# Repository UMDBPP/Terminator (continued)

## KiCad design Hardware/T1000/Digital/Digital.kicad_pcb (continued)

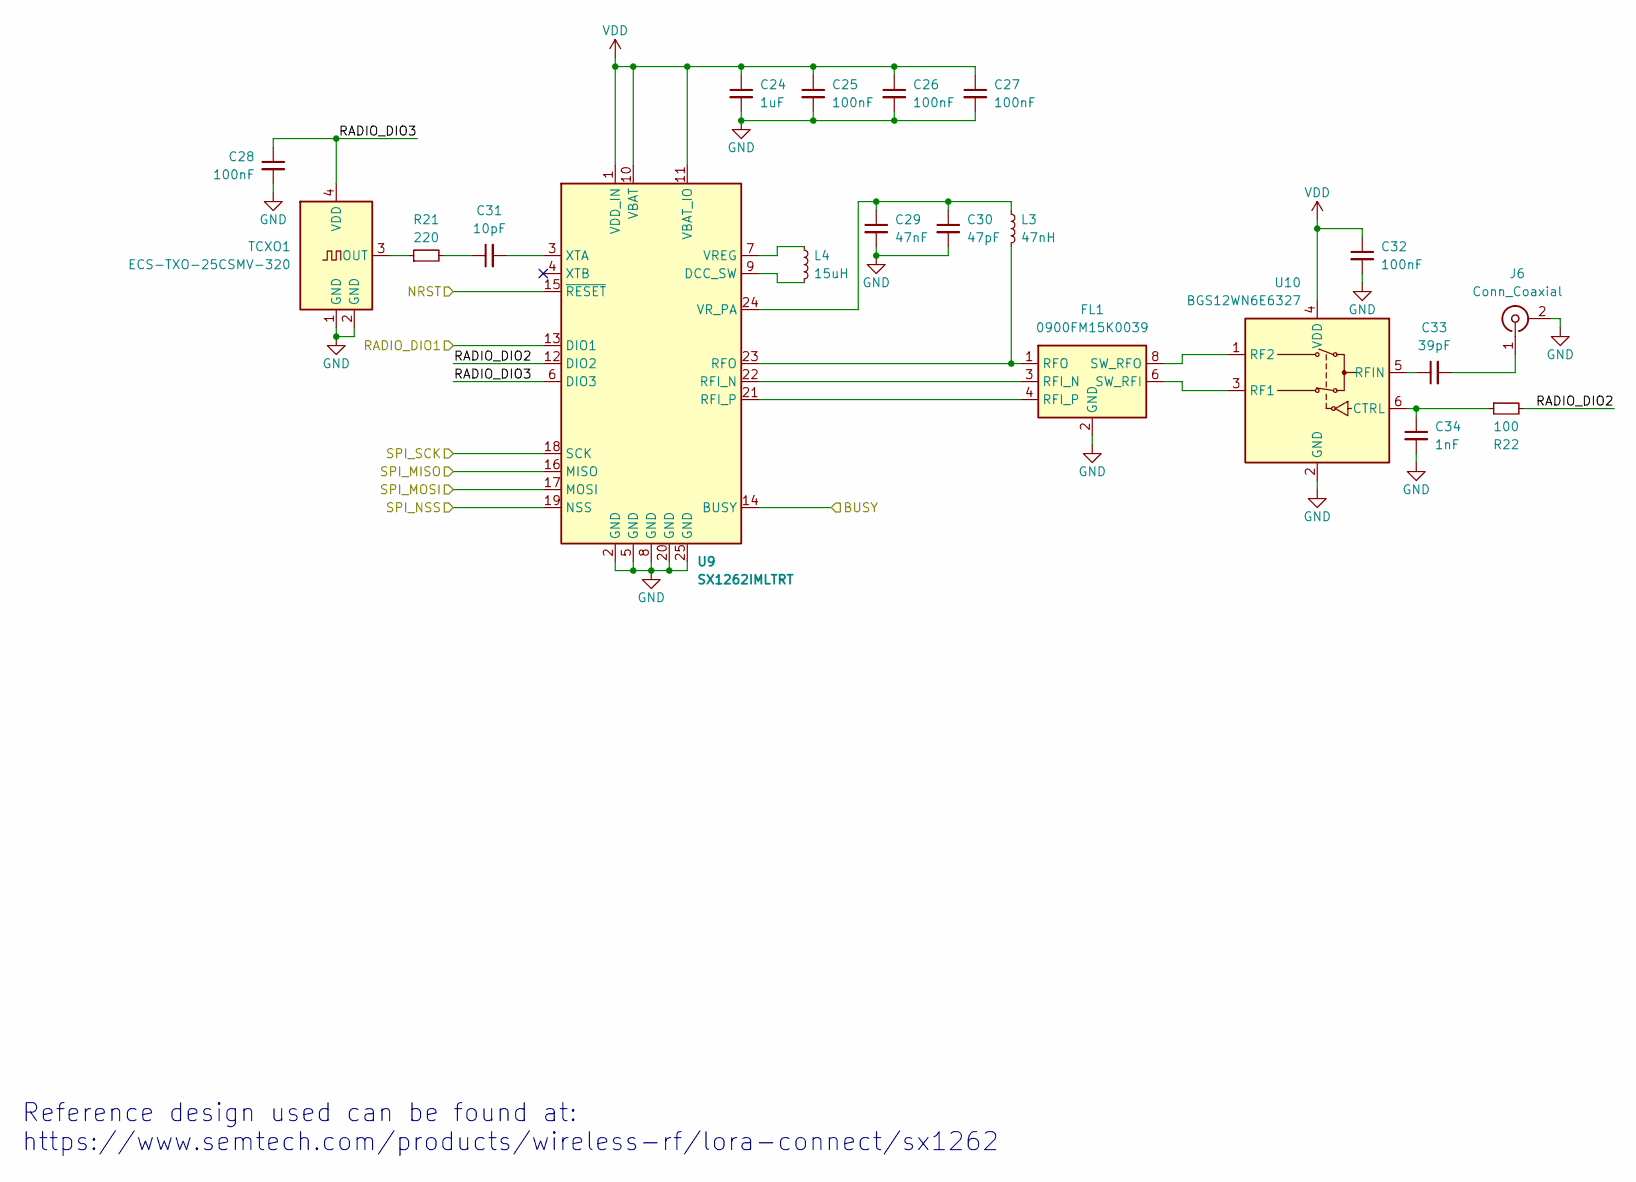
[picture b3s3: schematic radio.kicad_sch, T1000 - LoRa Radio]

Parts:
C24: 1uF; C_0603_1608Metric
C25, C26, C27, C28, C32: 100nF; C_0402_1005Metric
C29: 47nF; C_0402_1005Metric
C30: 47pF; C_0402_1005Metric
C31: 10pF; C_0402_1005Metric
C33: 39pF; C_0402_1005Metric
C34: 1nF; C_0402_1005Metric
FL1: 0900FM15K0039; Balun_Johanson_0900FM15K0039
J6: Conn_Coaxial; U.FL_Molex_MCRF_73412-0110_Vertical
L3: 47nH; L_0402_1005Metric
L4: 15uH; L_0805_2012Metric
R21: 220; R_0402_1005Metric
R22: 100; R_0402_1005Metric
TCXO1: ECS-TXO-25CSMV-320; Crystal_SMD_2520-4Pin_2.5x2.0mm
U9: SX1262IMLTRT; QFN-24-1EP_4x4mm_P0.5mm_EP2.6x2.6mm
U10: BGS12WN6E6327; Infineon_PG-TSNP-6-10_0.7x1.1mm_0.7x1.1mm_P0.4mm

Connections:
/LoRa Radio/RADIO_DIO2: R22.2, U9.12 (DIO2)
/LoRa Radio/RADIO_DIO3: C28.1, TCXO1.4 (VDD), U9.6 (DIO3)
/RADIO_BUSY: U9.14 (BUSY); also elsewhere on the board
/RADIO_DIO1: U9.13 (DIO1); also elsewhere on the board
/RADIO_NSS: U9.19 (NSS); also elsewhere on the board
/SPI1_MISO: U9.16 (MISO); also elsewhere on the board
/SPI1_MOSI: U9.17 (MOSI); also elsewhere on the board
/SPI1_SCK: U9.18 (SCK); also elsewhere on the board
/T_NRST: U9.15 (~RESET); also elsewhere on the board
GND: C24.2, C25.2, C26.2, C27.2, C28.2, C29.2, C30.2, C32.2, C34.2, FL1.2 (GND), FL1.5 (GND), FL1.7 (GND), FL1.9 (GND), FL1.10 (GND), J6.2 (Ext), TCXO1.1 (GND), TCXO1.2 (GND), U9.2 (GND), U9.5 (GND), U9.8 (GND), U9.20 (GND), U9.25 (GND), U10.2 (GND); also elsewhere on the board
unnamed: C31.1, R21.2
unnamed: FL1.3 (RFI_N), U9.22 (RFI_N)
unnamed: FL1.4 (RFI_P), U9.21 (RFI_P)
unnamed: FL1.1 (RFO), L3.2, U9.23 (RFO)
unnamed: FL1.6 (SW_RFI), U10.3 (RF1)
unnamed: FL1.8 (SW_RFO), U10.1 (RF2)
unnamed: C33.2, J6.1 (In)
unnamed: R21.1, TCXO1.3 (OUT)
unnamed: L4.2, U9.9 (DCC_SW)
unnamed: L4.1, U9.7 (VREG)
unnamed: C29.1, C30.1, L3.1, U9.24 (VR_PA)
unnamed: C31.2, U9.3 (XTA)
unnamed: C34.1, R22.1, U10.6 (CTRL)
unnamed: C33.1, U10.5 (RFIN)
VDD: C24.1, C25.1, C26.1, C27.1, C32.1, U9.1 (VDD_IN), U9.10 (VBAT), U9.11 (VBAT_IO), U10.4 (VDD); also elsewhere on the board

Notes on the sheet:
Reference design used can be found at: https://www.semtech.com/products/wireless-rf/lora-connect/sx1262

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
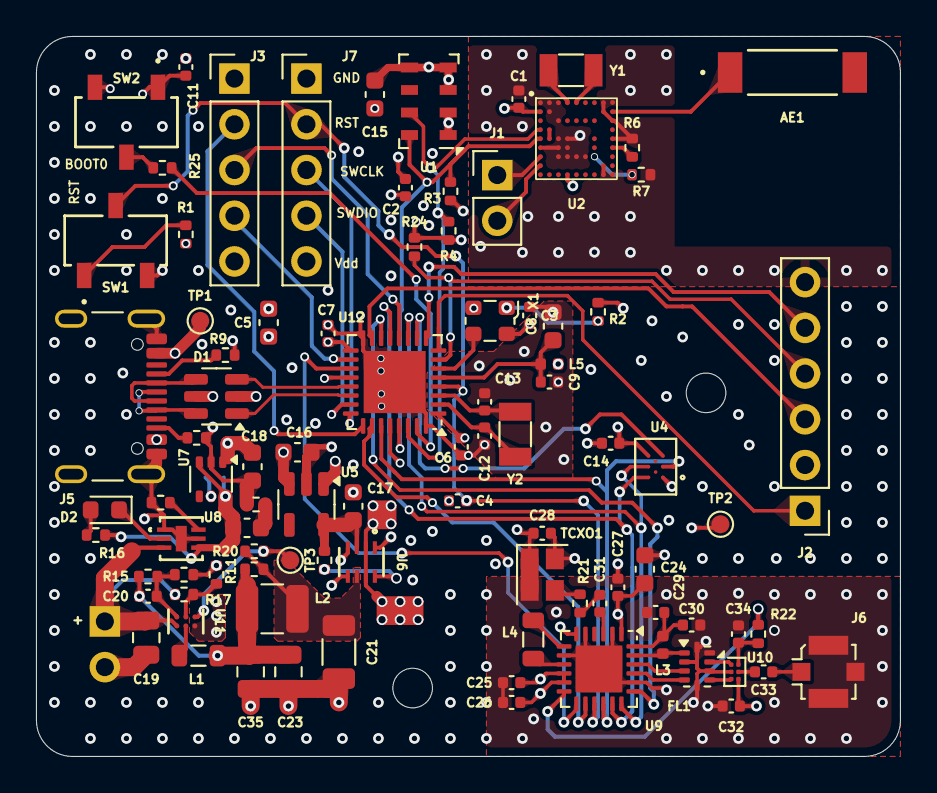
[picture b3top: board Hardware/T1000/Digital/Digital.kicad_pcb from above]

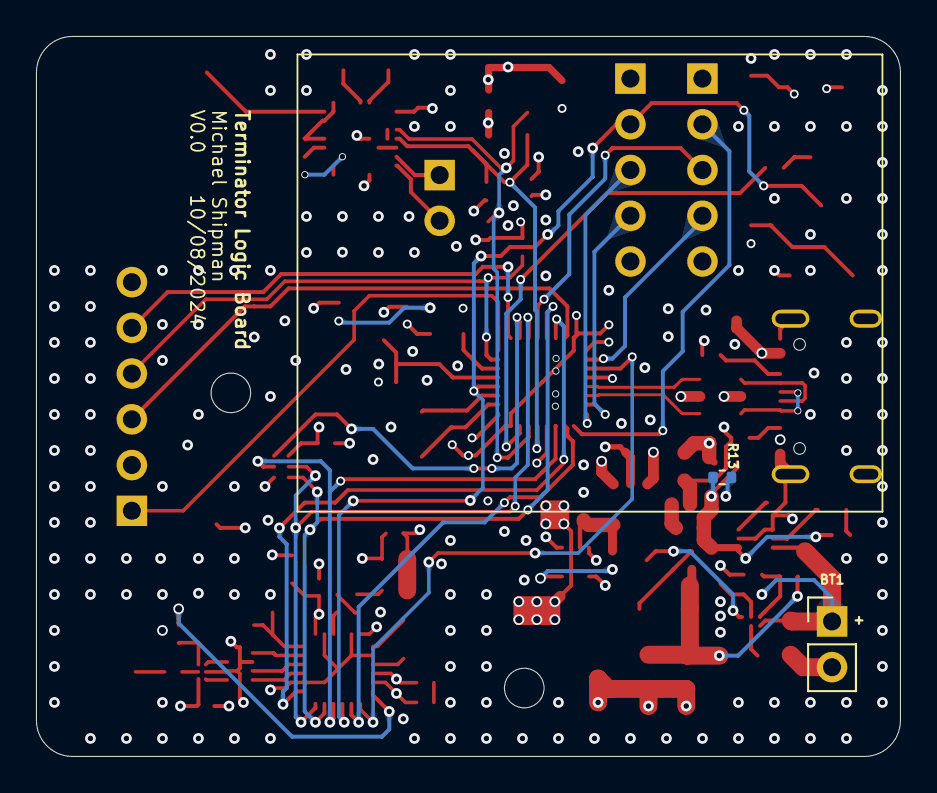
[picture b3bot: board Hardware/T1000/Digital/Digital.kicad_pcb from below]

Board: 6 copper layers, 48.0 x 40.0 mm, 95 parts (2 on the bottom side), 76 nets.

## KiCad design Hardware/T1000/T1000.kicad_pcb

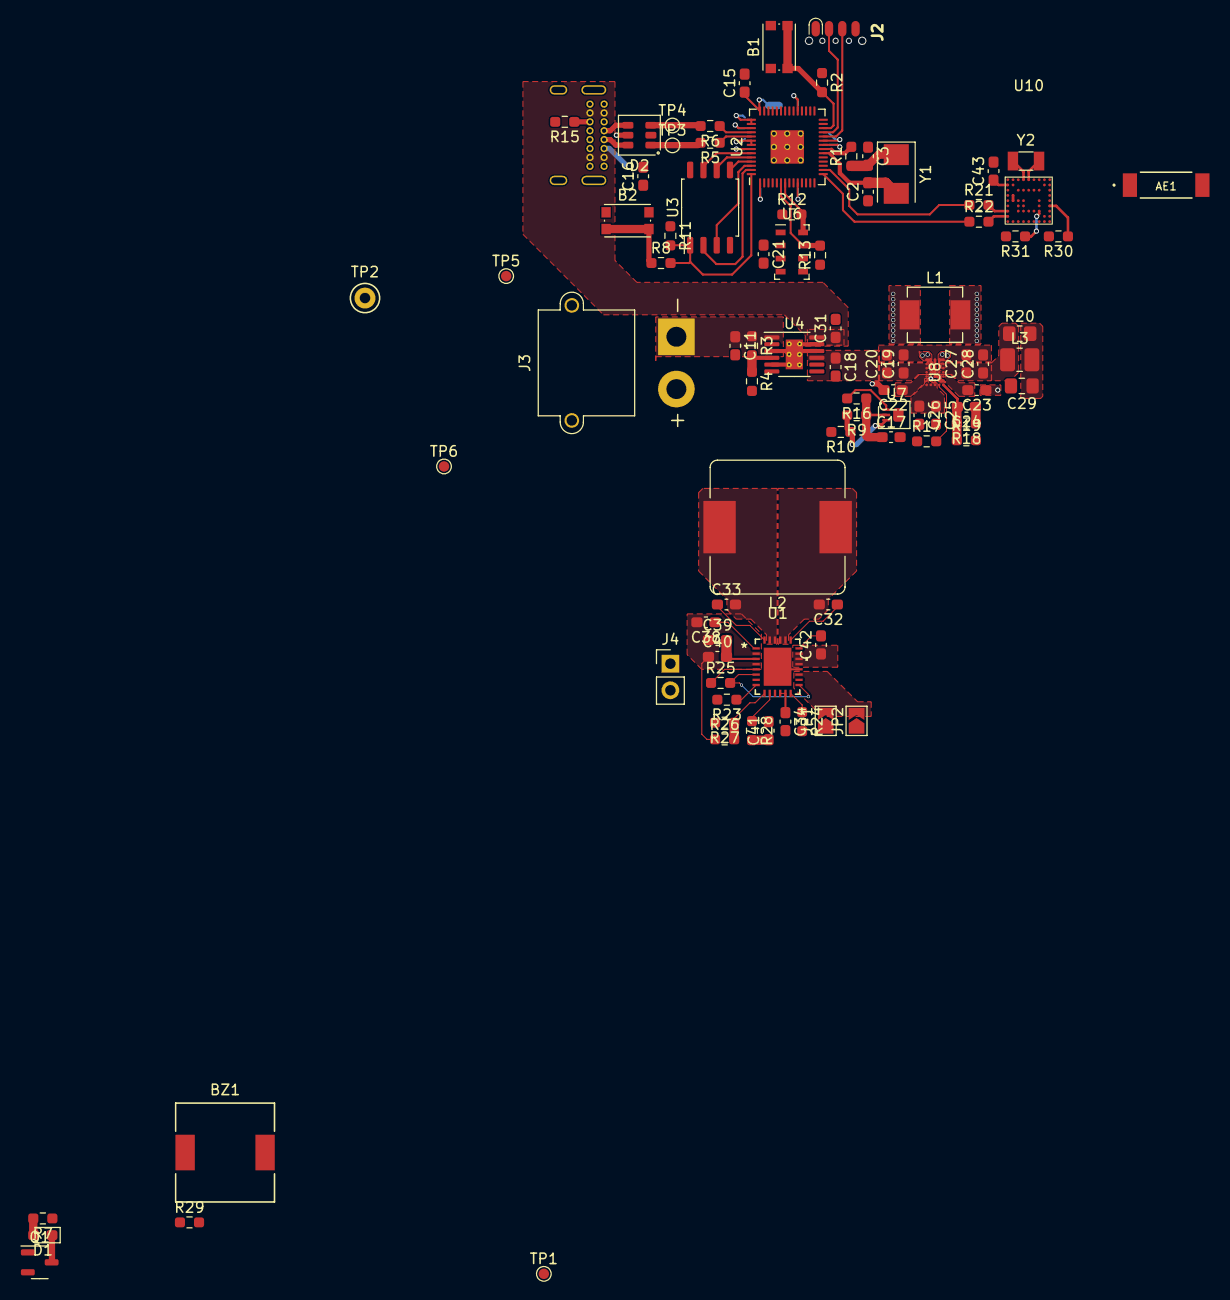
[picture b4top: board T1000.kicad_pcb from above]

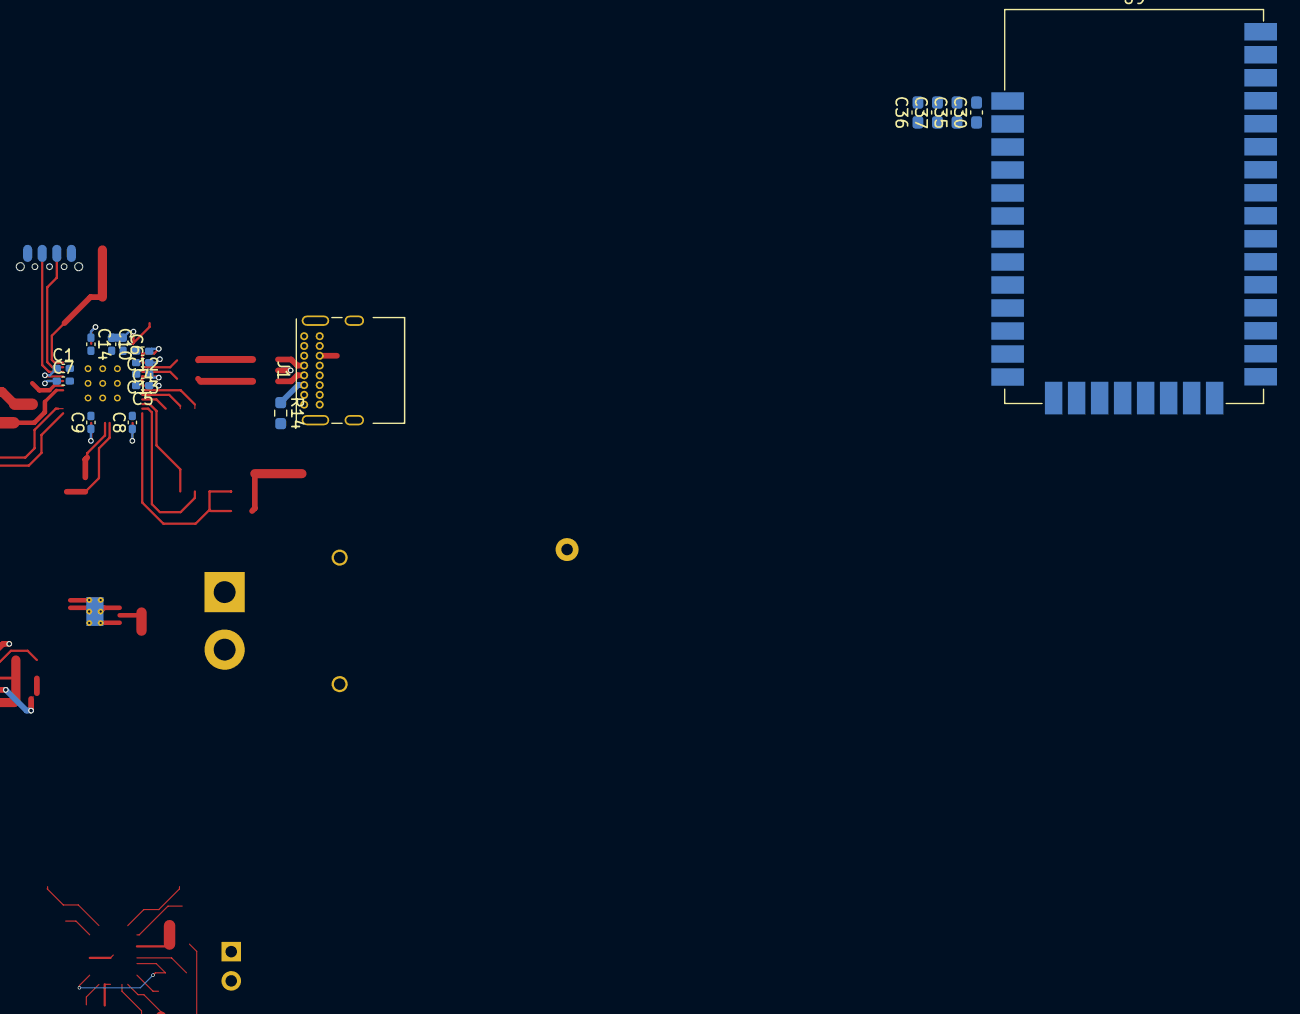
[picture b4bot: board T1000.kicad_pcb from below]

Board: 4 copper layers, 107 parts (18 on the bottom side), 68 nets.

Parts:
AE1: Antenna; ANT_1575AT_JOT-M
B1, B2: KMR2; SW_Push_1P1T_NO_CK_KMR2
BZ1: Buzzer; PKMCS0909E4000-R1_MUR
C1, C4, C7, C8, C9, C10, C12, C13, C14: 100nF; C_0402_1005Metric_Pad0.74x0.62mm_HandSolder
C2, C3: 22pF; C_0603_1608Metric_Pad1.08x0.95mm_HandSolder
C5, C6: 1uF; C_0402_1005Metric_Pad0.74x0.62mm_HandSolder
C11, C25, C31: 2.2uF; C_0603_1608Metric_Pad1.08x0.95mm_HandSolder
C15, C18, C19, C20, C27, C28, C30, C42: 10uF; C_0603_1608Metric_Pad1.08x0.95mm_HandSolder
C16, C21, C35, C43: 100nF; C_0603_1608Metric_Pad1.08x0.95mm_HandSolder
C17: 1uF; C_0603_1608Metric_Pad1.08x0.95mm_HandSolder
C22, C23, C32, C33: 220nF; C_0603_1608Metric_Pad1.08x0.95mm_HandSolder
C24: 10pF; C_0603_1608Metric_Pad1.08x0.95mm_HandSolder
C26: 470nF; C_0603_1608Metric_Pad1.08x0.95mm_HandSolder
C29: 15uF; C_0805_2012Metric_Pad1.18x1.45mm_HandSolder
C34: 4.7uF; C_0603_1608Metric_Pad1.08x0.95mm_HandSolder
C36: 47pF; C_0603_1608Metric_Pad1.08x0.95mm_HandSolder
C37: 8.2pF; C_0603_1608Metric_Pad1.08x0.95mm_HandSolder
C38: 22nF; C_0603_1608Metric_Pad1.08x0.95mm_HandSolder
C39, C40: 22uF; C_0603_1608Metric_Pad1.08x0.95mm_HandSolder
C41: 680p; C_0603_1608Metric_Pad1.08x0.95mm_HandSolder
D1: LED; D_0603_1608Metric_Pad1.05x0.95mm_HandSolder
D2: USBLC6-2SC6; SOT-23-6
J1: USB_C_Receptacle_USB2.0; USB_C_Receptacle_GCT_USB4085
J2: SOICbite; SOIC_clipProgSmall
J3: XT30; AMASS_XT30PW-M_1x02_P2.50mm_Horizontal
J4: Nichrome; PinHeader_1x02_P2.54mm_Vertical
JP1, JP2: SolderJumper_2_Open; SolderJumper-2_P1.3mm_Open_TrianglePad1.0x1.5mm
L1: 1.5uH; L_Vishay_IHLP-2020
L2: 3.3uH; L_Bourns_SRP1265A
L3: 3.3uH; L_1008_2520Metric_Pad1.43x2.20mm_HandSolder
Q1: IRLML0060TRPBF; SOT-23-3
R1, R8: 1k; R_0603_1608Metric_Pad0.98x0.95mm_HandSolder
R2, R11, R12, R13: 10k; R_0603_1608Metric_Pad0.98x0.95mm_HandSolder
R3: 1M; R_0603_1608Metric_Pad0.98x0.95mm_HandSolder
R4: 715k; R_0603_1608Metric_Pad0.98x0.95mm_HandSolder
R5, R6: 27; R_0603_1608Metric_Pad0.98x0.95mm_HandSolder
R7: 590; R_0603_1608Metric_Pad0.98x0.95mm_HandSolder
R9: 1.05M; R_0603_1608Metric_Pad0.98x0.95mm_HandSolder
R10, R26, R27: 154k; R_0603_1608Metric_Pad0.98x0.95mm_HandSolder
R14, R15: 5.1k; R_0603_1608Metric_Pad0.98x0.95mm_HandSolder
R16: 510k; R_0603_1608Metric_Pad0.98x0.95mm_HandSolder
R17: 16.9k; R_0603_1608Metric_Pad0.98x0.95mm_HandSolder
R18: 178k; R_0603_1608Metric_Pad0.98x0.95mm_HandSolder
R19: 20k; R_0603_1608Metric_Pad0.98x0.95mm_HandSolder
R20: 100m; R_0805_2012Metric_Pad1.20x1.40mm_HandSolder
R21, R22: 33; R_0603_1608Metric_Pad0.98x0.95mm_HandSolder
R23: 81.1k; R_0603_1608Metric_Pad0.98x0.95mm_HandSolder
R24: 75k; R_0603_1608Metric_Pad0.98x0.95mm_HandSolder
R25: 5m; R_0603_1608Metric_Pad0.98x0.95mm_HandSolder
R28: 56.2k; R_0603_1608Metric_Pad0.98x0.95mm_HandSolder
R29: 100; R_0603_1608Metric_Pad0.98x0.95mm_HandSolder
R30, R31: 0; R_0603_1608Metric_Pad0.98x0.95mm_HandSolder
TP1, TP3, TP4, TP5, TP6: TestPoint; TestPoint_Pad_D1.0mm
TP2: TestPoint; TestPoint_Keystone_5000-5004_Miniature
U1: LT3120JV-PBF; LQFN28_Rev0_ADI-M
U2: RP2040; RP2040-QFN-56
U3: W25Q128JVS; SOIC-8_5.23x5.23mm_P1.27mm
U4: LTC4419; MSOP-12-1EP_3x4mm_P0.65mm_EP1.65x2.85mm_ThermalVias
U6: MS5607-02BA; LGA-8_3x5mm_P1.25mm
U7: LT6703CDC-3; DFN-3-1EP-2x2mm_P0.5mm_EP1x1.35mm
U8: MAX77857; MAX77857-35WLP
U9: XBee_SMT; Digi_XBee_SMT
U10: MIA-M10Q
Y1: 445I23D12M00000; Crystal_SMD_5032-2Pin_5.0x3.2mm
Y2: 32.768k; Crystal_SMD_3215-2Pin_3.2x1.5mm

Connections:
+1V1: C1.1, C4.1, C5.1, U2.23 (DVDD), U2.45 (VREG_VOUT), U2.50 (DVDD)
+3V3: C6.1, C7.1, C8.1, C9.1, C10.1, C12.1, C13.1, C14.1, C15.1, C16.1, C21.1, C29.1, C30.1, C35.1, C36.1, C37.1, C43.1, J2.1, JP2.1 (A), L3.2, R2.1, R7.1, R11.1, R12.1, R13.1, R20.2, U2.1 (IOVDD), U2.10 (IOVDD), U2.22 (IOVDD), U2.33 (IOVDD), U2.42 (IOVDD), U2.43 (ADC_AVDD), U2.44 (VREG_IN), U2.48 (USB_VDD), U2.49 (IOVDD), U3.8 (VCC), U6.1 (VDD), U6.2 (PS), U9.2 (VCC), U10.B1 (VCC), U10.J4 (V_IO), U10.J5 (V_BCKP)
+BATT: C11.1, J3.1, JP1.1 (A), R3.1, R25.1, U1.5 (ISP), U4.1 (V1)
+VDC: C17.1, C18.1, C19.1, C20.1, R9.1, R16.1, U4.9 (OUT), U7.2 (V+), U8.A4 (IN), U8.A5 (IN), U8.A6 (IN), U8.B4 (IN)
/D1: Q1.1 (G), U2.11 (GPIO8)
/GPS_RX: R22.1, U2.15 (GPIO12)
/GPS_TX: R21.1, U2.16 (GPIO13)
/LVC: R16.2, U1.16 (EN/UVLO), U7.1 (OUT), U8.B2 (EN), U8.B3 (EN)
/QSPI_SCLK: U2.52 (QSPI_SCLK), U3.6 (CLK)
/QSPI_SD0: U2.53 (QSPI_SD0), U3.5 (DI(IO0))
/QSPI_SD1: U2.55 (QSPI_SD1), U3.2 (DO(IO1))
/QSPI_SD2: U2.54 (QSPI_SD2), U3.3 (IO2)
/QSPI_SD3: U2.51 (QSPI_SD3), U3.7 (IO3)
/QSPI_SS: R8.2, R11.2, U2.56 (QSPI_SS), U3.1 (~CS)
/SCL: R12.2, TP6.1, U2.7 (GPIO5), U6.8 (SCLK)
/SDA: R13.2, TP5.1, U2.6 (GPIO4), U6.7 (SDI/SDA)
/USB_D+: D2.1 (L1), R5.2, TP3.1
/USB_D-: D2.3 (L2), R6.2, TP4.1
GND: B1.1, B2.1, BZ1.2 (+), C1.2, C2.1, C3.1, C4.2, C5.2, C6.2, C7.2, C8.2, C9.2, C10.2, C11.2, C12.2, C13.2, C14.2, C15.2, C16.2, C17.2, C18.2, C19.2, C20.2, C21.2, C25.2, C26.2, C27.2, C28.2, C29.2, C30.2, C31.2, C34.2, C35.2, C36.2, C37.2, C39.2, C40.2, C41.2, C42.2, C43.2, D2.2 (VN), J1.A1 (GND), J1.A12 (GND), J1.B1 (GND), J1.B12 (GND), J1.S1 (SHIELD), J2.4, J3.2, J4.2, Q1.2 (S), R4.2, R10.2, R14.2, R15.2, R17.1, R19.2, R23.2, R24.2, R27.2, R30.2, R31.2, TP2.1, U1.3 (GND), U1.11 (GND), U1.18 (GND), U1.22 (GND), U1.29 (PGND), U2.19 (TESTEN), U2.57 (GND), U3.4 (GND), U4.3 (CMP1), U4.5 (GND), U4.10 (CMP2), U4.11 (GND), U4.13 (GND), U6.3 (GND), U6.4 (CSB), U6.5 (CSB), U7.4 (V-), U8.C3 (PGND), U8.C4 (PGND), U8.C5 (PGND), U8.C6 (PGND), U8.C7 (PGND), U8.D2 (PGND), U8.D3 (PGND), U8.E2 (AGND), U9.1 (GND), U9.11 (GND), U9.13 (GND), U9.22 (GND), U9.35 (GND), U10.A1 (GND), U10.A2 (GND), U10.A3 (GND), U10.A8 (GND), U10.A9 (GND), U10.B2 (GND), U10.B8 (GND), U10.C3 (GND), U10.C9 (GND), U10.E3 (GND), U10.E4 (GND), U10.E9 (GND), U10.F1 (GND), U10.F3 (GND), U10.F4 (GND), U10.G3 (GND), U10.G4 (GND), U10.G5 (GND), U10.G6 (GND), U10.H8 (GND), U10.J8 (GND), U10.J9 (GND)
unnamed: AE1.1 (A), U10.B9 (RF_IN)
unnamed: B2.2, R8.1
unnamed: BZ1.1 (-), R29.2
unnamed: C3.2, R1.1, Y1.1
unnamed: C22.2, L1.1, U8.A7 (LX1), U8.B5 (LX1), U8.B6 (LX1), U8.B7 (LX1)
unnamed: C23.1, L1.2, U8.D5 (LX2), U8.D6 (LX2), U8.D7 (LX2), U8.E7 (LX2)
unnamed: C24.1, C27.1, C28.1, L3.1, R18.1, R20.1, U8.D4 (OUT), U8.E4 (OUT), U8.E5 (OUT), U8.E6 (OUT)
unnamed: C32.2, L2.1, U1.24 (SW1), U1.25 (SW1)
unnamed: C33.2, L2.2, U1.26 (SW2), U1.27 (SW2)
unnamed: C41.1, R28.2
unnamed: D1.2 (A), R7.2
unnamed: D1.1 (K), Q1.3 (D)
unnamed: D2.6 (L1), J1.A6 (D+), J1.B6 (D+)
unnamed: D2.4 (L2), J1.A7 (D-), J1.B7 (D-)
unnamed: J1.A5 (CC1), R14.1
unnamed: J1.B5 (CC2), R15.1
unnamed: J2.2, U2.25 (SWD)
unnamed: J2.3, U2.24 (SWCLK)
unnamed: C38.2, C39.1, C40.1, J4.1, R26.1, U1.2 (PVOUT), U1.4 (PVOUT)
unnamed: JP1.2 (B), JP2.2 (B), U1.17 (VIN)
unnamed: R30.1, U10.F9 (RSRVD)
unnamed: R31.1, U10.G7 (RSRVD)
unnamed: C32.1, U1.23 (BST1)
unnamed: C33.1, U1.28 (BST2)
unnamed: C38.1, U1.1 (BST3)
unnamed: R26.2, R27.1, U1.9 (FB)
unnamed: C42.1, R25.2, U1.6 (ISN), U1.15 (SYNC/MODE), U1.19 (PVIN), U1.20 (PVIN), U1.21 (PVIN)
unnamed: C34.1, U1.12 (MPCC), U1.13 (VCC)
unnamed: R23.1, U1.8 (PROG)
unnamed: R24.1, U1.14 (RT)
unnamed: R28.1, U1.10 (VC)
unnamed: R29.1, U2.13 (GPIO10)
unnamed: B1.2, R2.2, U2.26 (RUN)
unnamed: R6.1, U2.46 (USB_DM)
unnamed: R5.1, U2.47 (USB_DP)
unnamed: C2.2, U2.20 (XIN), Y1.2
unnamed: R1.2, U2.21 (XOUT)
unnamed: R3.2, R4.1, U4.4 (ADJ)
unnamed: R9.2, R10.1, U7.3 (IN+)
unnamed: C22.1, U8.A3 (BST1)
unnamed: C23.2, U8.E3 (BST2)
unnamed: C24.2, R18.2, R19.1, U8.E1 (FB)
unnamed: C25.1, C26.1, U8.A1 (SCL), U8.A2 (VIO), U8.B1 (SDA), U8.C1 (VL)
unnamed: R17.2, U8.D1 (SEL)
unnamed: U10.A4 (RTC_I), Y2.2
unnamed: U10.A5 (RTC_O), Y2.1
unnamed: R22.2, U10.H1 (RX)
unnamed: R21.2, U10.G1 (TX)
VBUS: C31.1, D2.5 (VP), J1.A4 (VBUS), J1.A9 (VBUS), J1.B4 (VBUS), J1.B9 (VBUS), TP1.1, U4.12 (V2)

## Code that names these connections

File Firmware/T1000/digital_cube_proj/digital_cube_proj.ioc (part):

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Mcu.Name=STM32L422KBUx
Mcu.Package=UFQFPN32
Mcu.UserName=STM32L422KBUx
PA0-CK_IN.Mode=HSE-External-Clock-Source-for-LittleOrca
PA0-CK_IN.Signal=RCC_CK_IN
PA1.Mode=INP
PA1.Signal=COMP1_INP
PA10.Signal=S_TIM1_CH3
PA15\ (JTDI).Signal=USART2_RX
PA2.Signal=ADCx_IN7
PA3.Signal=ADCx_IN8
PA4.Signal=GPIO_Output
PA5.Mode=Full_Duplex_Master
PA5.Signal=SPI1_SCK
PA7.Mode=Full_Duplex_Master
PA7.Signal=SPI1_MOSI
PA9.Signal=GPIO_Input
PB0.Signal=GPIO_Output
PB1.Mode=PWM Generation3 CH3 CH3N
PB1.Signal=TIM1_CH3N
PB3\ (JTDO/TRACESWO).Signal=GPIO_Input
PB4\ (NJTRST).Mode=Full_Duplex_Master
PB4\ (NJTRST).Signal=SPI1_MISO
PB6.Mode=I2C
PB6.Signal=I2C1_SCL
PB7.Mode=I2C
PB7.Signal=I2C1_SDA
PC14-OSC32_IN\ (PC14).Mode=LSE-External-Oscillator
PC14-OSC32_IN\ (PC14).Signal=RCC_OSC32_IN
PC15-OSC32_OUT\ (PC15).Mode=LSE-External-Oscillator
PC15-OSC32_OUT\ (PC15).Signal=RCC_OSC32_OUT
RCC.HSE_VALUE=25000000
RCC.SYSCLKFreq_VALUE=25000000
RCC.SYSCLKSource=RCC_SYSCLKSOURCE_HSE
board=custom

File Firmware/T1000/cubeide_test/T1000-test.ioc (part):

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Mcu.Name=STM32L422TBYx
Mcu.Package=WLCSP36
Mcu.UserName=STM32L422TBYx
PA0-CK_IN.Mode=HSE-External-Clock-Source-for-LittleOrca
PA0-CK_IN.Signal=RCC_CK_IN
PA10.Signal=S_TIM1_CH3
PA11.Mode=Device
PA11.Signal=USB_DM
PA12.Mode=Device
PA12.Signal=USB_DP
PA13\ (JTMS/SWDIO).Mode=Serial_Wire
PA13\ (JTMS/SWDIO).Signal=SYS_JTMS-SWDIO
PA14\ (JTCK/SWCLK).Mode=Serial_Wire
PA14\ (JTCK/SWCLK).Signal=SYS_JTCK-SWCLK
PA2.Signal=ADCx_IN7
PA4.Mode=NSS_Signal_Hard_Output
PA4.Signal=SPI1_NSS
PA5.Mode=Full_Duplex_Master
PA5.Signal=SPI1_SCK
PA7.Mode=Full_Duplex_Master
PA7.Signal=SPI1_MOSI
PB1.Mode=Forced Output3 CH3 CH3N
PB1.Signal=TIM1_CH3N
PB2.Mode=INP
PB2.Signal=COMP1_INP
PB4\ (NJTRST).Mode=Full_Duplex_Master
PB4\ (NJTRST).Signal=SPI1_MISO
PB7.Mode=I2C
PB7.Signal=I2C1_SDA
PB8.Mode=I2C
PB8.Signal=I2C1_SCL
PC14-OSC32_IN\ (PC14).Mode=LSE-External-Oscillator
PC14-OSC32_IN\ (PC14).Signal=RCC_OSC32_IN
PC15-OSC32_OUT\ (PC15).Mode=LSE-External-Oscillator
PC15-OSC32_OUT\ (PC15).Signal=RCC_OSC32_OUT
RCC.HSE_VALUE=25000000
RCC.SYSCLKFreq_VALUE=25000000
RCC.SYSCLKSource=RCC_SYSCLKSOURCE_HSE
board=custom

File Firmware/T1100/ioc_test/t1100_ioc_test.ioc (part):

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Mcu.Name=STM32WLE5JCIx
Mcu.Package=UFBGA73
Mcu.UserName=STM32WLE5JCIx
PA10.Signal=S_TIM1_CH3
PA4.Signal=GPIO_Output
PA5.Signal=GPIO_Output
PB0-VDD_TCXO.Mode=HSE-TCXO
PB0-VDD_TCXO.Signal=VDDTCXO
PB13.Mode=IN0
PB13.Signal=ADC_IN0
PB15.Signal=GPIO_Output
PB3.Mode=Full_Duplex_Master
PB3.Signal=SPI1_SCK
PB4.Mode=Full_Duplex_Master
PB4.Signal=SPI1_MISO
PB5.Mode=Full_Duplex_Master
PB5.Signal=SPI1_MOSI
PB6.Mode=I2C
PB6.Signal=I2C1_SCL
PB7.Mode=I2C
PB7.Signal=I2C1_SDA
PB9.Mode=PWM Generation3 CH3 CH3N
PB9.Signal=TIM1_CH3N
PC0.Mode=Asynchronous
PC0.Signal=LPUART1_RX
PC1.Mode=Asynchronous
PC1.Signal=LPUART1_TX
PC14-OSC32_IN.Mode=LSE-External-Oscillator
PC14-OSC32_IN.Signal=RCC_OSC32_IN
PC15-OSC32_OUT.Mode=LSE-External-Oscillator
PC15-OSC32_OUT.Signal=RCC_OSC32_OUT
RCC.HSE_VALUE=8000000
RCC.SYSCLKFreq_VALUE=32000000
board=custom

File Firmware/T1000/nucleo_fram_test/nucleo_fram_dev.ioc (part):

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Mcu.Name=STM32L412R8Tx
Mcu.Package=LQFP64
Mcu.UserName=STM32L412R8Tx
PA7.Mode=PWM Generation1 CH1 CH1N
PA7.Signal=TIM1_CH1N
PA8.Signal=S_TIM1_CH1
PB13.Signal=SPI2_SCK
PB14.Signal=SPI2_MISO
PB15.Signal=SPI2_MOSI
PB6.Signal=GPIO_Output
RCC.HSE_VALUE=8000000
board=custom

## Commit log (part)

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2023-07-31 init hardware
2023-07-31 added SD card
2023-08-02 buck-boost initial implementation
2023-08-03 schematic updates
2023-08-14 filter tuning
2023-09-11 started layout
2023-09-12 more layout
2023-09-13 little bit of routing, changed to MIA-M10 GPS to make my life harder
2023-09-13 bringing it together, also managed to crash Kicad so this commit can be considered under duress in a court of law
2024-09-06 created digital and RF combo board and did most of the layout
2024-09-06 some library updates
2024-09-06 T1000 exports folder and schematic
2024-09-07 Update .gitignore to ignore DS_Store
2024-09-12 V0 changes before order
2024-09-13 basic firmware build system created
2024-09-13 clean up and some documentation
2024-09-13 added HAL and more documentation
2024-09-13 automatic dependency and include for HAL code in makefile now
2024-09-19 basic cutdown power stage sim
2024-09-19 added source for fancy makefile
2024-09-19 started working with LL drivers
2024-09-23 first pass at ez gpio function
2024-10-08 started STM32 package change (T1001)
2024-10-09 ordered T1001
2024-10-11 FRAM SPI device id read works
2024-10-12 littlefs port complete, boot_count demo working
2024-10-15 FRAM demo cleaned up a little and packaged into nice folder for it
2024-10-15 working PWM generation
2024-10-15 complemented PWM (sometimes need power reset?)
2024-10-17 PI loop test, mixed results
2024-10-17 ADC test, works but not as well as needed
2024-10-22 created project for digital board
2024-10-22 massing pushing to update devboard test projects
2024-10-22 helper functions and I2C
2024-10-27 NS-129 basic flight code
2024-10-27 added boot_count to log
2024-10-28 added GPIO signal for logging event
2024-10-29 V0.1 of cutdown board to add opamp scaling on current sense
2024-10-29 added cutdown README
2024-10-29 copid rp2040 ms5607 driver in, still need to port I2C transactions
2024-10-31 added finicky MS5607 driver, not working right unsure if SW/HW
2024-11-04 updated GPS parsing to be more readable
2024-11-08 added a number of things but notably PID now that new power board is in, also GPS USART2 RX on PA15 header so that I can use an external GPS for now, all needs testing
2024-11-09 prelim PID is working, holding the current sense voltage at about the correct value, also added internal watchdog timer
2024-11-12 refactored some existing code after second cold box test
2024-11-12 testing data directory added
2024-11-12 sx1262 code compiles, not tested
2024-11-18 code flown on NS-130
2024-11-23 optimizing PID loop, at 20.52 us right now
2024-11-23 boosted core clock to 80 MHz for PID testing, down to 6.4 us loop time as expected
2024-12-09 committing cause I finished my final report for ENEE499L
2025-02-10 never pushed final testing files
2025-02-10 pushing these for completetion, not important
2025-02-14 cutdown power stage V1.0 changes
2025-04-23 T1100 testing directory
2025-08-05 saving changes before I mess around with sub ghz middleware
2025-08-07 got radio to enter TX mode according to status/error flags, need to confirm with spectrum analyzer
2025-08-09 code for NS-134, working TX and heater, sometimes working GPS (hardware issue)
2026-03-11 clean up DS_Store
2026-03-11 clean up and move and add T1100 stuff
2026-03-11 update kicad-lib
2026-03-11 updates to T1000 code (this is so out of order)
2026-03-11 T1000 NS-130 back up
2026-03-11 remove more DS_Store
2026-03-11 remove dupe directory
2026-04-16 Update T1100 code to prove LPUART1 works
